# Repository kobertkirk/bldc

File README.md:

# 48 V / 35 A BLDC hub-motor controller

A KiCad hardware design plus STM32 firmware for a hall-sensored e-bike or scooter hub motor:

* **48 V nominal** (13S Li-ion, 54.6 V full). All power parts are rated 100 V and the TVS clamps at 60 V standoff.
* **35 A battery current limit** and 60 A phase current limit. Both are set in firmware and can be changed over UART.
* **Field-oriented control (FOC)** using the hall sensors, with angle interpolation, for quiet and smooth torque from standstill.
* **Throttle** input (standard 0.8–4.2 V hall throttle).
* **Momentary power button.** Press to switch on, hold for 2 s to switch off. Standby current is a few µA.
* **FWD/REV switch** input (switch to GND = reverse). There is also a **brake** input (switch to GND = cut power, optional regen).
* **UART telemetry and commands** (115200 8N1, 3.3 V). It streams every reading: voltage, currents, power, speed, temperatures, throttle, direction, faults, limits and energy used.
* **Auto-detect** measures motor R and L and learns the hall-sensor table, so any 120° hall hub motor works without setting angles by hand.

```
hardware/
  kicad/                 KiCad project (bldc48.kicad_pro): 4-sheet schematic + routed 4-layer PCB
  renders/               3D renders, routing/layer images, bldc48.glb 3D model
  bldc48-schematic.pdf   schematic as PDF
  bom.csv                bill of materials
  tools/                 circuit.py (the netlist source), generators, autorouting, connectivity checker,
                         render3d/ (VRML export + headless three.js renderer)
firmware/
  src/                   STM32G431 firmware (register-level, no HAL)
  sim/                   closed-loop PC simulation of the firmware against a hub-motor model
  cmsis/                 ST / ARM CMSIS headers (Apache-2.0)
```

> **Status — read this before building.** The schematic is complete and has been checked pin by pin (see
> [Verification](#verification)). The 90 × 95 mm (3.5 × 3.7 in) 4-layer, two-sided PCB (rev F) is **fully routed and passes KiCad
> DRC with 0 violations and 0 unconnected pads**. The power stage is placed by script around fixed columns; the signal
> routing was done by an autorouter (Freerouting), a small grid router for what it leaves open, and scripted copper
> pours, so have it reviewed before ordering. The firmware compiles and passes a detailed simulation, but it has
> **not been run on real hardware**. Bring the first board up with the current-limited procedure in
> [First power-up](#first-power-up).

---

## Block diagram

```
 BAT+ ──┬── TVS ── 3×1000µF + 6×2.2µF ──┬────────────────────────────────────┐
        │                                │  3 × half bridge (6 × IPT015N10N5) │
        │        ┌──────── DRV8353RS ────┴── GHx / GLx gate drive, SHx sense  ├── MOTOR A/B/C
        │        │  charge pump, 6-95 V buck → +5 V ── AP2112 → +3.3 V        │
        ├─Q1─────┤  3 × current-sense amp (G=20) ◄── 0.5 mΩ low-side Kelvin shunts
        │ latch  │  SPI config / fault readout, nFAULT
  PWR ──┘        └──► STM32G431CB ◄── ISENSE A/B/C, VBUS, throttle, NTCs
  button               │  ▲
              UART ◄───┘  └── halls, FWD/REV, brake, button
```

## Connectors

| Ref | Connector | Pin 1 | Pin 2 | Pin 3 | Pin 4 | Pin 5 | Pin 6 |
|---|---|---|---|---|---|---|---|
| J1 / J2 | 12 AWG solder pads (2.8 mm hole), right of the bridge | BAT+ / BAT− | | | | | |
| J3–J5 | 12 AWG solder pads, one per phase column | MOTOR A / B / C | | | | | |
| HALL | JST-GH 6 | +5 V | GND | Hall A | Hall B | Hall C | Motor NTC (optional) |
| THROTTLE | JST-GH 3 | +5 V | Signal | GND | | | |
| FWD/REV | JST-GH 2 | DIR (to GND = reverse) | GND | | | | |
| BRAKE | JST-GH 2 | BRAKE (to GND = braking) | GND | | | | |
| POWER_BTN | JST-GH 2 | PWR_SW (momentary to GND) | GND | | | | |
| UART | JST-GH 4 | +3.3 V out | TX (board → host) | RX (host → board) | GND | | |
| SWD | JST-GH 5 | +3.3 V | SWDIO | SWCLK | NRST | GND | |

All signal connectors are JST-GH (1.25 mm, latching) along the bottom edge. The power button and all signal wires
carry 3.3–5 V only, never battery voltage, so a cheap handlebar button is fine. Battery and phase wires are **12 AWG
silicone wire soldered straight into the plated pads** (strip 4 mm, push through, solder from the top; the pads are
via-stitched to the pours on all layers). Strain-relieve the wires to the case or heat plate with a cable tie so the
joints never carry the cable's weight. Put an **XT90-S anti-spark connector** and a **40 A fuse** in the battery
lead: the board has no reverse-polarity or inrush protection.

## First power-up

1. Flash the firmware over SWD (`cd firmware && make flash`).
2. Use a **bench supply at 48 V with a 2 A current limit**. Connect the UART (3.3 V USB-serial adapter at 115200 baud)
   and the halls, but leave the motor phases disconnected. Press the power button: the green LED blinks and telemetry
   lines (`$TLM,...`) appear. Type `status`. You should see vbus ≈ 48 V and `faults NOT_DETECTED`. Type `drv`:
   it should report `nFAULT=high` and zero status words (the DRV8353RS took its SPI settings).
3. Connect the motor phases (any order) and the hall connector. **Lift the wheel** so it spins freely.
4. Type `detect`. The wheel turns slowly forwards and then backwards (about 15 s total). Expected result:
   `detect OK: R = … mOhm, L = … uH, halls learned`. Type `save`.
   *(No UART cable? Hold the brake and full throttle for 3 s right after power-up, then release the throttle. Detect
   runs and saves automatically.)*
5. With the wheel still lifted, apply a little throttle. If the wheel turns the wrong way, `set dir_invert 1` then `save`.
6. Raise the supply limit (or switch to the battery) and set your limits, e.g. `set i_batt_max 35`, `set i_phase_max 60`,
   then `save`.

## UART interface

Lines end with CR or LF. Replies start with `>`. Telemetry lines start with `$TLM` (default every 100 ms;
change with `stream <ms>` or `stream off`).

```
$TLM,ms,state,faults,limits,vbus,ibus,power,ia,ib,ic,id,iq,iq_ref,erpm,rpm,mod,thr_v,thr_pct,dir,brake,hall,t_fet,t_mot,wh,ah,wh_regen
$TLM,105500,IDLE,0000,00,51.99,0.00,0.0,-0.01,0.01,-0.10,0.06,-0.00,0.00,2670,116.1,0.000,0.849,0.0,FWD,0,4,25.0,nan,10.912,0.2224,0.000
```
(Real line from the simulation: a coasting wheel at 116 rpm, 52 V, throttle at rest. `t_mot` is `nan` when no motor
NTC is enabled.)

| Command | What it does |
|---|---|
| `help` | List the commands |
| `status` | Human-readable state, faults, voltage, current, rpm, temperatures and control-loop CPU load |
| `tlm` / `hdr` | Print one telemetry line / print the column names |
| `stream <ms>` / `stream off` | Set the periodic telemetry rate, or turn it off |
| `get [name]` | Show one parameter, or all of them (including the learned hall angles) |
| `set <name> <value>` | Change a parameter in RAM |
| `save` / `defaults` | Write the config to flash / reload the defaults into RAM |
| `detect` / `detect r` / `detect l` / `detect hall` | Run auto-detect: everything, or only R, L or the hall table |
| `clear` | Clear latched faults |
| `drv` | DRV8353RS fault/status words, live and as captured at the last driver trip |
| `off` / `reboot` | Power the board off / restart the MCU |

Main parameters (`get` lists them all): `i_phase_max` 60 A, `i_batt_max` 35 A, `i_batt_regen` 5 A, `i_brake` 0 A (regen
on the brake input, off by default), `v_uv_start` 42 V / `v_uv_cut` 39 V (13S), `v_ov` 60 V, `t_fet_start` 80 °C /
`t_fet_max` 100 °C, `thr_min_v` 1.0 V / `thr_max_v` 4.0 V, `ramp_up` 100 A/s, `erpm_max` 0 (no speed limit),
`pole_pairs` 23 (only affects the rpm display), `mot_ntc_en` 0, `auto_off_min` 0.

| Fault bit (`faults` field, hex) | Meaning | Red LED blinks |
|---|---|---|
| 0x001 | overcurrent (80 A instantaneous phase-current trip) | 1 |
| 0x002 | overvoltage (> `v_ov`) | 2 |
| 0x004 | battery below `v_uv_cut` (no torque; information only) | short blink every 2 s |
| 0x008 | hall sensors invalid (000/111, e.g. unplugged) | 4 |
| 0x010 | throttle wire fault (< 0.4 V or > 4.7 V) | 5 |
| 0x020 | FET over-temperature or NTC broken | 6 |
| 0x040 | motor over-temperature (if `mot_ntc_en`) | 7 |
| 0x080 | halls not learned yet (run `detect`) | 8 |
| 0x100 | last detect failed | 9 |
| 0x200 | current-sensor offset out of range | 10 |
| 0x400 | throttle held at power-up | 11 |
| 0x800 | gate driver fault (DRV8353 nFAULT: VDS overcurrent, gate fault, UVLO, over-temperature); `drv` shows the fault words; the driver is re-initialised before it clears | 12 |

`limits` bits (why torque is reduced right now): 0x01 battery current, 0x02 phase current, 0x04 undervoltage
fold-back, 0x08 FET temperature, 0x10 motor temperature, 0x20 speed limit, 0x40 out of voltage (top speed),
0x80 stall protection.

Faults switch the gates off at once. They clear by themselves once the cause is gone and the throttle is back at
zero, so the motor can never restart while the throttle is held.

## How it works

**Power stage.** Six Infineon IPT015N10N5 (100 V, 1.5 mΩ, TOLL package) are driven directly by a TI DRV8353RS
smart gate driver (100 V, SPI). It sets the gate current itself (300 mA source / 600 mA sink, ≈100 ns edges on these
FETs), so there are no gate resistors; it adds 100 ns of its own dead time on top of the MCU's 400 ns and has a VDS
short-circuit trip (0.3 V, ≈110 A at 125 °C) behind the firmware's 80 A trip. Its SHx inputs sense each switch node
at the high-side source, right next to the gate pin. The MCU's TIM1 generates 20 kHz centre-aligned complementary
PWM (6-input mode). With the main output disabled, or with the driver asleep, all six gates are held low.

**Current sensing.** A 0.5 mΩ 4-terminal (Kelvin) shunt sits in each low-side source (Bourns CSS4J-4026R-L500F,
5 W). Its sense pads go to one of the DRV8353RS's three current-sense amplifiers (gain 20, biased to mid-rail), so full
scale is ±165 A per phase, comfortably above the 80 A hard trip (a compile-time check enforces this). The ADCs sample
while all three low-side FETs conduct, triggered by TIM1 channel 4 just before the counter peak. Above 90 % duty one
phase's low-side window is too short, so that phase's current is rebuilt from the other two (Ia + Ib + Ic = 0); the
duty is capped at 97 % so the bootstrap capacitors always recharge.

**Control.** The ADCs are triggered by the PWM timer once per period, and the injected-conversion interrupt runs the
FOC loop at 20 kHz:
- Clarke and Park transforms.
- PI current regulators on d and q, with BEMF/cross-coupling feed-forward and conditional-integration anti-windup.
- PWM delay compensation.
- Min/max SVPWM, capped at 97 % (low-side sensing needs a short low-side window; see above).

The rotor angle comes from the halls. Each hall edge gives the exact boundary angle, and between edges the angle is
extrapolated using a speed averaged over a full electrical revolution, which cancels sensor placement error. At
standstill the sector centre is used, which guarantees at least 86 % torque from the very first moment.

**Limits.**
- Throttle sets the torque (iq), with a ramp.
- Phase current limit.
- Battery current limit, from the power balance `I_bat = 1.5·vq·iq / Vbus`. In simulation it holds 34.8 A against a 35 A setting.
- Undervoltage, FET/motor temperature, speed and stall fold-backs.
- Instant 80 A hard trip and overvoltage trip.
- A direction change is only accepted once the wheel has stopped.

The motor flux linkage is learned while riding and used to re-engage smoothly at speed.

**Power latch.** When the button is pressed it pulls Q1's base (MMBTA92, 300 V PNP) low through 47 k and a diode.
Q1 enables the DRV8353RS's buck regulator. The MCU then sets PWR_HOLD, which turns on Q2 (MMBTA42) to keep Q1 on. A
BAT46W blocks the button-sense pull-up, so the latch cannot creep on through the unpowered 3.3 V rail. The buck's
enable divider also gives a ≈20 V UVLO. On shutdown the MCU first puts the gate driver to sleep, then releases the latch.

**Supplies.** The DRV8353RS's built-in 6–95 V buck (LM5008A core) makes +5 V for the halls, throttle and the
AP2112K-3.3 LDO; its 100 µH inductor is a 6 × 6 mm Bourns SRN6045TA. The gate drive comes from the DRV8353's own
charge pump (high side) and VGLS regulator (low side), so there is no 12 V rail and no separate gate-driver supply.
On power-up the firmware writes the driver's five configuration registers over SPI, reads them back and locks them;
a driver that does not answer stops the motor from starting (`drv` shows why).

## Verification

* `hardware/tools/check_netlist.py` exports KiCad's own netlist and checks that **every pin of all 133 parts** sits on
  the intended net, with no single-node nets. KiCad 7's CLI has no ERC, so this replaces it. A deliberately miswired
  pin is caught.
* KiCad DRC on the routed PCB: **0 violations, 0 unconnected pads, 0 footprint errors**, including the check that
  every footprint matches the stock KiCad library (report: `hardware/kicad/routing/drc.rpt`).
* `cd firmware && make sim` runs the **real** `motor.c`/`hall.c`/`cli.c` in closed loop against a model with:
  dead-time, PWM delay, ADC noise and offsets, 120° halls at an arbitrary offset, a 100 kg rider and a battery with
  internal resistance. It does this for two different motors. Results for motor 1:

  | Check | Result |
  |---|---|
  | Detect R / L / hall angles | 119.9 mΩ (120) / 259 µH (250) / 0.2° worst error |
  | Start from standstill, full throttle | torque ≥ 86 % of command from the first instant |
  | Peak phase current | 60.2 A (limit 60 A) |
  | Peak battery current (100 ms avg) | 34.3 A (limit 35 A) |
  | 120 A phase-short spike | hard trip, gates off within 200 µs |
  | Gate-driver fault (nFAULT) while riding | gates off within 2 PWM periods, driver re-initialised before restart |
  | High-duty current rebuild (low-side shunts) | exercised continuously at top speed, no faults |
  | Current-loop tracking | 0.47 A rms |
  | Top speed, 26″ wheel | ≈ 39 km/h (voltage limited) |
  | Coast, re-engage at speed, reverse, brake, throttle-wire break, hall unplug, low battery, overvoltage | all pass |

## Building the firmware

```
sudo apt install gcc-arm-none-eabi libnewlib-arm-none-eabi   # plus stlink-tools or openocd
cd firmware
make            # build/bldc48.elf/.bin/.hex  (~38 KB flash)
make flash      # st-flash, or: make flash-ocd
make sim        # closed-loop simulation on the PC
```

## Regenerating the hardware

The schematic, PCB and BOM are generated from `hardware/tools/circuit.py`, using symbols and footprints from the stock
KiCad libraries. After you edit the circuit, run `hardware/tools/regen.sh`. It needs KiCad ≥ 7; KiCad 8 and 9 open the
files directly.

`regen.sh` only places the parts. The board was then routed with
`hardware/tools/route_pcb.py --legacy --no-optimize --passes 30 --freerouting freerouting-1.9.0.jar`. This script:
- keeps tracks off the inner layers under the FETs, DC-link caps and shunts, and off the outer layers across the
  switch-node and low-side copper (rule areas)
- gives every GND pad outside the power stage its own via into the solid In1 plane, and puts a fixed "sense tap" via
  in each switch node next to the high-side gate pin for the DRV8353's SHx input
- routes the signals with Freerouting (headless, under `xvfb-run`)
- imports the result (KiCad 7 can only import a Specctra session from its GUI, so the script parses the file
  itself and restores any layer-change vias the router left out)
- `astar_route.py` is a small 4-layer grid router for connections Freerouting leaves open, keeping clear of the
  power copper
- adds the GND / +48V / +3V3 planes, the 35 A outer-layer pours and via arrays in the power pads, routes anything
  still cut off into its own pour, and stitches pour islands to the planes
- fills the zones and writes a DRC report

The routing session is saved in `hardware/kicad/routing/bldc48.ses` (with the DRC report next to it); `route_pcb.py
--ses ../kicad/routing/bldc48.ses` rebuilds a routed board from it, taking the part positions from the session. The
committed `bldc48.kicad_pcb` is the reference: a rebuild can differ in a few fan-out vias and then needs a DRC pass.

`hardware/tools/render3d/render.sh` exports the board to VRML with the KiCad 3D models (plus simple stand-ins for the
JST-GH connectors, the SRN6045 inductor and the DRV8353 QFN, whose models are not in the KiCad 7 library) and renders
the PNGs in `hardware/renders/` with three.js in headless Chromium; `layers.sh` makes the copper-layer images.

**Note:** regenerating overwrites placement and routing. For changes after this point, edit the board in KiCad and use
Tools → Update PCB from Schematic. The footprints are already linked to their schematic symbols for that.

### Board

| Overview | Power stage |
|---|---|
|  |  |
|  |  |

Routing (tracks only, pours hidden): 

Copper layers: [top](hardware/renders/bldc48-layer-top.png) · [inner 1, GND](hardware/renders/bldc48-layer-in1.png) ·
[inner 2, +48V/+3V3](hardware/renders/bldc48-layer-in2.png) · [bottom](hardware/renders/bldc48-layer-bottom.png)

Stackup as built: F.Cu power stage, gate drive and signals, with pours (switch nodes, low-side sources, +48V bus,
GND fill) · In1.Cu solid GND plane · In2.Cu +48V under the power stage and +3V3 fill elsewhere, plus signals ·
B.Cu the same high-current pours under the bridge, the MCU and I/O parts, and signals. The inner planes are unbroken
under the FETs, DC-link caps and shunts. 1666 track segments and 269 vias; each switch-node and low-side pour is one
unbroken piece on both outer layers (checked by script).

## Rev F: DRV8353RS, 90 × 95 mm

Rev E (180 × 69.5 mm) was still too big. Rev F redesigns the circuit around one TI DRV8353RS smart gate driver and
puts the parts on both sides of a **90 × 95 mm** board, **68 % of rev E's area** (3.5 × 3.7 in instead of
7.1 × 2.7 in).
- **One chip instead of eight.** The DRV8353RS replaces the three LM5109B gate drivers, the three INA240A1 current
  amplifiers and both LM5164 bucks: it has the gate drive (charge pump + low-side regulator, no 12 V rail), three
  current-sense amplifiers and a 6–95 V buck that makes the +5 V rail.
- **Low-side shunts.** The three 0.5 mΩ Kelvin shunts now sit in the low-side sources (the DRV8353's amplifiers are
  low-side). The firmware samples while all low-side FETs conduct and rebuilds the third current above 90 % duty.
- **Three 1000 µF / 100 V** cans (Aishi ERS1KM102M35OT, 18 × 35 mm) in a column next to the bridge, plus two 2.2 µF
  ceramics straight across each half bridge. 3000 µF is still 1.7 × rev B's 1760 µF. Cans can be bent over before
  soldering if the case is low.
- **12 AWG wires soldered straight into the board** instead of M5 bolt terminals: battery pads at the right of the
  bridge, one motor pad per phase column. JST-GH (1.25 mm, latching) for all signal connectors.
- **Two-sided assembly.** Power stage, gate driver, supply and connectors on top; MCU, its filters and the I/O
  conditioning on the bottom, outside the heat-plate area under the FETs.
- The phase columns run C-B-A from left to right, following the DRV8353's pin order, so no phase's gate drive crosses
  another's. The labels are only names: auto-detect learns the hall/phase order.
- Signal tracks 0.2 mm with 0.15 mm clearance (JLCPCB's 4-layer minimum is 0.09 mm). The +48 V and switch-node pours
  keep 0.5 mm.

Each phase is a column: high-side FET, low-side FET, shunt, two 2.2 µF ceramics and the motor wire pad on the switch
node beside the FETs. The heat plate goes under the bridge (bottom side, no parts there).

## Ordering from JLCPCB (rough cost)

These are estimates from JLCPCB's published pricing and LCSC part prices in October 2026. Upload the files to get a
real quote, because their prices change often.

| Item (order of 5 assembled boards) | Approx. |
|---|---|
| 4-layer PCB 90 × 95 mm, 1.6 mm, 2 oz outer copper, 5 pcs | $30–50 |
| PCBA setup + stencils, **two-sided** (standard PCBA: both sides placed) | ≈ $50 |
| "Extended" LCSC part loading fee, ≈ $3 per unique part type (~22 types) | ≈ $65 |
| SMT + through-hole joints (≈ 530 SMT + 6 THT per board) | ≈ $10 |
| Parts (≈ $30/board, all from LCSC; the DRV8353RS is ≈ $6, the six FETs ≈ $15) | ≈ $150 |
| Shipping (DHL / FedEx) | $20–35 |
| **Total for 5** | **≈ $325–360, about $65–72 per board** |

The five 12 AWG wire pads are left for you to solder (wires are not assembled). Choosing JLCPCB's "economic" PCBA
is not possible for a board with parts on both sides; if cost matters more than size, rev E (one-sided, 180 ×
69.5 mm) is in the git history.

Every part in the BOM has an LCSC part number or is a generic resistor/capacitor/diode/connector that LCSC stocks in
quantity, so JLCPCB can build the whole board.
- The bulk capacitors are Aishi ERS1KM102M35OT (C724666): 1000 µF/100 V, 18 × 35 mm, 7.5 mm pitch, 10 000 h at
  105 °C. Aishi's "1K" voltage code is 100 V in its own scheme ("1B" is 80 V), and LCSC lists the part as 100 V.
- Ripple: at 35 A battery current the DC link carries roughly 17 A rms, ≈ 5.7 A per can with three cans; the ceramics
  take the high-frequency part. Expect the cans to run warm in sustained hard use: watch their temperature, or lower
  `i_batt_max` / `i_phase_max`, or fit higher-ripple parts (Panasonic EEU-FC2A102, Nichicon UHE2A102).
- The shunts are Bourns CSS4J-4026R-L500F (LCSC/JLCPCB C2076423, 0.5 mΩ ±1 %, 5 W, 4-terminal). The footprint is
  KiCad's `R_Shunt_Isabellenhuette_BVR4026` (same 10.6 mm span and pad layout).
- The DRV8353RS is TI DRV8353RSRGZR (LCSC C506246), VQFN-48 7 × 7 mm with an exposed pad. Its exposed pad has a
  thermal-via array into the GND plane; ask for the vias to be tented or plugged.
- Check that every part you order has a 100 V rating where the BOM needs one: the TOLL FETs, DRV8353RS, the
  1000 µF/100 V caps, the 100 V ceramics and the SS110 diode. Do not let the assembly service substitute
  lower-voltage parts.
- Set the stackup to 2 oz outer copper. JLCPCB's cheap 4-layer offer is 1 oz.
- JLCPCB only assembles from 2 boards upward, and the setup and part-loading fees are charged once per order, so
  most of the cost of a small order is fees.
- Board size: 90 × 95 mm (3.5 × 3.7 in), 1.6 mm thick. The 1000 µF caps are the tallest parts, so the assembled
  board is about 37 mm tall (less if the caps are bent over). Four M3 holes: two in the battery strip, two in the
  bottom corners.

## Design review (rev B, kept for reference)

A full review of rev A found and fixed these problems:

| Problem in rev A | Fix in rev B |
|---|---|
| BAT+ / BAT− were 5×10 mm SMD solder pads 7.5 mm apart (≈2.5 mm copper gap), 6 mm in from the edge; SMD pads tear off under 12 AWG wire strain | M5 plated bolt terminals for ring lugs, via-stitched to the planes, on the left edge 36 mm apart, TVS between them, large BAT+/BAT− silkscreen |
| Motor pads sat 38 mm below their shunts | M5 bolt terminals on the bottom edge straight below each shunt, labelled MOTOR A/B/C |
| **Overcurrent trip could never fire**: INA240A2 (gain 50) saturated the ADC at ±66 A, below the 80 A trip | INA240A1 (gain 20, ±165 A full scale); a compile-time assert keeps the trip inside the measurable range; new simulation test trips on a 120 A spike within 200 µs |
| INA240 inputs tapped the switch-node/phase copper anywhere, so pour resistance corrupted the current reading | 4-terminal Kelvin shunt (Bourns CSS4J-4026R-L500F, 5 W) with dedicated sense pads to the amplifier |
| FET temperature sensor TH1 was in the board corner, far from the FETs | TH1 next to the middle low-side FET |
| DC-link ceramics ~32 mm from the low-side sources (large switching loop) | Ceramics directly under each low-side FET's source leads; both FETs drain-tab up so the switch node is a short gap between them |
| Low-side gate on the far side of the FET from its driver | Driver beside the FET pair, both gate pins facing it |
| Router ran signals on In2 straight under the FETs, slotting the +48V plane between the drains and the ceramics | Rule area keeps tracks off both inner layers under the FETs, ceramics and shunts |
| 10 Ω gate resistors: ≈170 ns edges, ≈2.9 W switching loss per high-side FET at 35 A | 4.7 Ω: ≈100 ns edges, ≈1.7 W |
| 6 × 220 µF carried ≈2.8 A rms ripple each | 8 × 220 µF, ≈2.1 A each |
| Pours sized from pad centres missed the TOLL drain tabs' real outline (vias in the tabs connected on one layer only) | Pours drawn from the measured pad outlines; inner planes solid-connected to the power terminals |

Checks run on rev B: every symbol pin matches its footprint pad (29 symbol/footprint pairs), every pin of all 174
parts is on its intended net, every footprint matches the stock KiCad library, KiCad DRC 0 violations, firmware
simulation passes on two motors including the new overcurrent test.

## PCB layout rules

* Use 4 layers with 2 oz outer copper. Run 35 A battery and phase paths as wide pours on two or more layers,
  stitched with many vias. Rule areas keep signal tracks off the switch-node and low-side copper on the top layer;
  do not route across them.
* Keep each half-bridge loop (high FET → low FET → 2.2 µF ceramics) as small as possible. The bulk caps sit right
  next to the bridge.
* Give the FET drain/source pads thermal-via arrays down to the bottom pours. Bolt the board to an aluminium plate or
  the case through a thermal pad under the bridge (no parts on the bottom there). At 35 A, expect roughly 6–10 W of
  losses at full load.
* Route each shunt's sense pads (pins 2/3 of the 4-terminal shunt) to the DRV8353's SPx/SNx as a pair, with the
  1 nF filter caps at the driver.
* Keep the gate-drive traces short and away from the switch nodes; the DRV8353's SHx pin senses each switch node at
  the high-side source, next to the gate pin. Use one solid ground plane, and keep the MCU and analog parts away from
  the switching nodes.
* Keep TH1 (the NTC) next to the low-side FETs, which run hottest.

## Things to double-check against datasheets before ordering

* The DRV8353RS buck (LM5008A core) component values (RT / shutdown divider, 100 µH inductor, 4.02 k / 4.02 k
  feedback divider, 8.2 k / 47 nF / 330 pF ripple injection) were chosen with the datasheet formulas but not run
  through TI WEBENCH.
* The DRV8353's gate-current setting (300 mA / 600 mA) and the gate-drive trace lengths: the longest gate trace is
  ≈ 60 mm (phase C high side). The driver's current-mode drive tolerates this, but look at the gate waveform on the
  first board and lower IDRIVE if it rings.
* The bulk capacitor ripple rating (≈ 5.7 A rms per can at 35 A battery current; see above).
* Choose `v_uv_*` for your pack. The defaults are for 13S.

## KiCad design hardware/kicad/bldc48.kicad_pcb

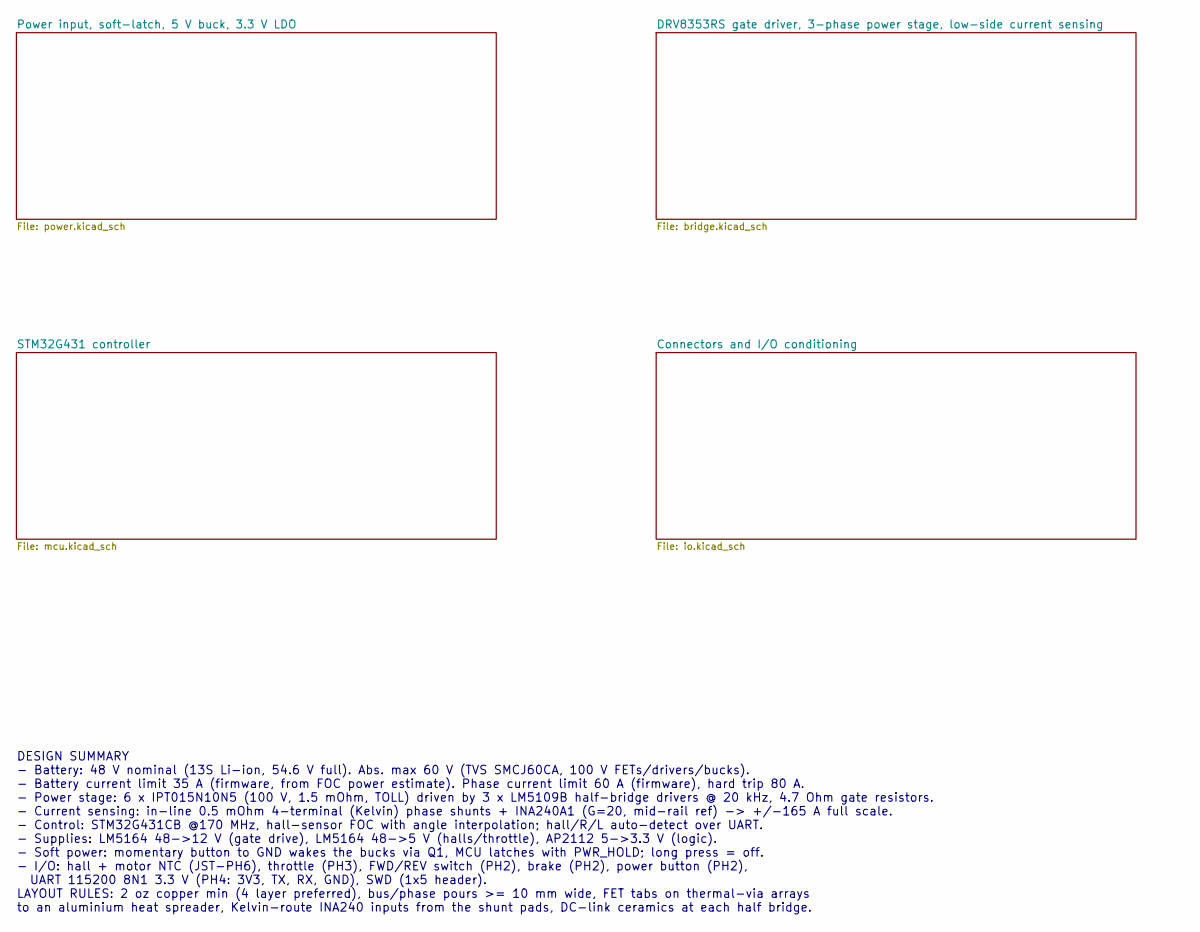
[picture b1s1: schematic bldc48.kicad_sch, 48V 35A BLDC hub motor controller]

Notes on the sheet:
DESIGN SUMMARY - Battery: 48 V nominal (13S Li-ion, 54.6 V full). Abs. max 60 V (TVS SMCJ60CA, 100 V FETs/drivers/bucks). - Battery current limit 35 A (firmware, from FOC power estimate). Phase current limit 60 A (firmware), hard trip 80 A. - Power stage: 6 x IPT015N10N5 (100 V, 1.5 mOhm, TOLL) dri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

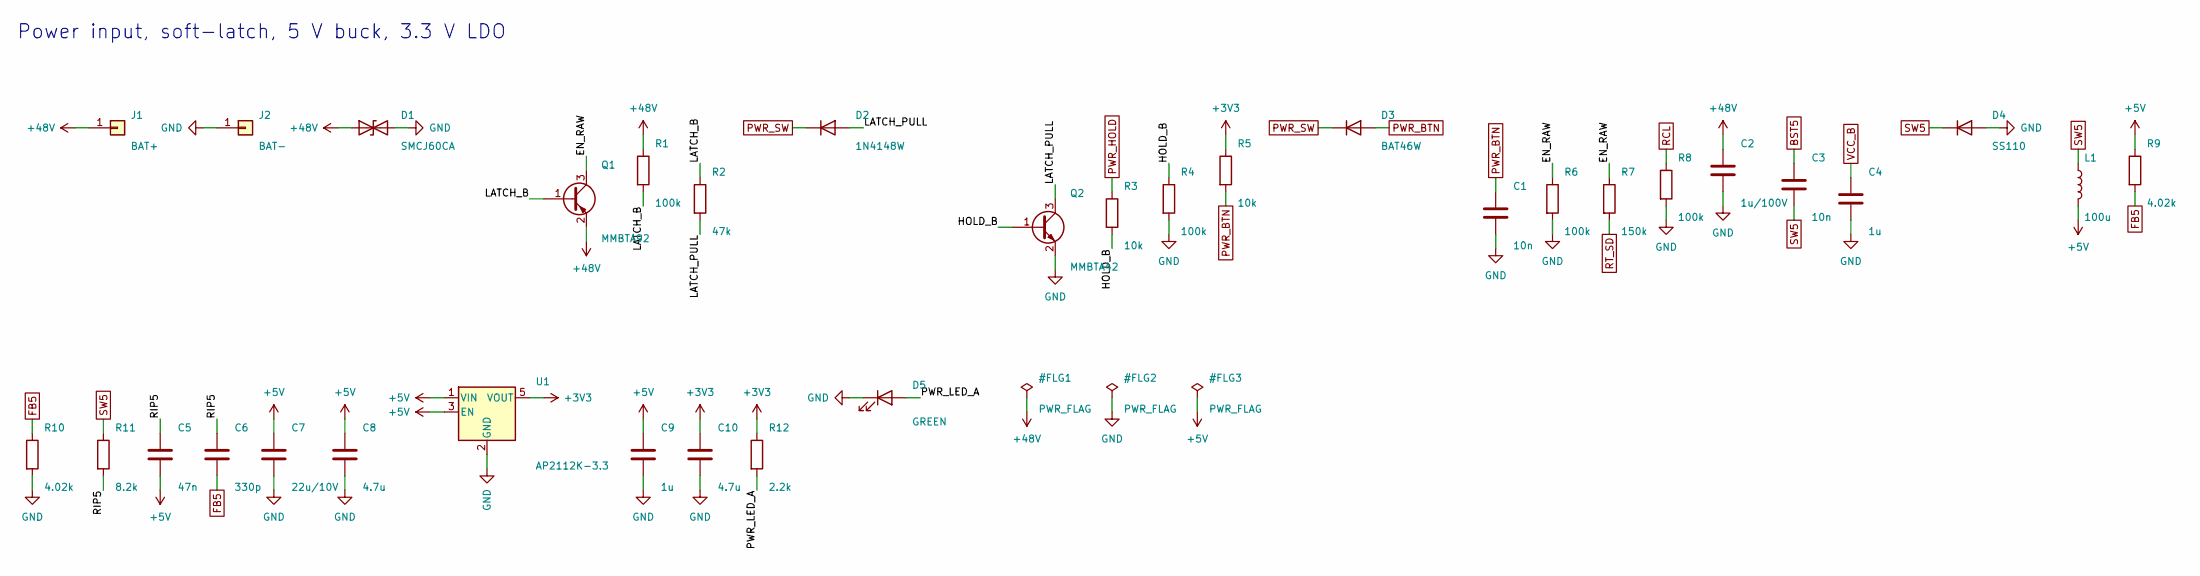
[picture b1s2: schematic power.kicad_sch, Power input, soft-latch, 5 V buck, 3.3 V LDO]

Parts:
C1, C3: 10n; C_0603_1608Metric
C2: 1u/100V; C_0805_2012Metric
C4, C9: 1u; C_0603_1608Metric
C5: 47n; C_0603_1608Metric
C6: 330p; C_0603_1608Metric
C7: 22u/10V; C_1210_3225Metric
C8, C10: 4.7u; C_0805_2012Metric
D1: SMCJ60CA; D_SMC
D2: 1N4148W; D_SOD-123
D3: BAT46W; D_SOD-123
D4: SS110; D_SMA; MPN 100 V 1 A Schottky, SMA (e.g. MDD SS110)
D5: GREEN; LED_0603_1608Metric
J1: BAT+; SolderWire_12AWG_D2.8mm_OD5.4mm; MPN 12 AWG wire, soldered
J2: BAT-; SolderWire_12AWG_D2.8mm_OD5.4mm; MPN 12 AWG wire, soldered
L1: 100u; L_Bourns_SRN6045TA; MPN Bourns SRN6045TA-101M or eq. (100 uH, I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
Q1: MMBTA92; SOT-23
Q2: MMBTA42; SOT-23
R1, R4, R6, R8: 100k; R_0603_1608Metric
R2: 47k; R_0603_1608Metric
R3, R5: 10k; R_0603_1608Metric
R7: 150k; R_0603_1608Metric
R9, R10: 4.02k; R_0603_1608Metric
R11: 8.2k; R_0603_1608Metric
R12: 2.2k; R_0603_1608Metric
U1: AP2112K-3.3; SOT-23-5

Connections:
+3V3: C10.1, R5.1, R12.1, U1.5 (VOUT); also elsewhere on the board
+5V: C5.2, C7.1, C8.1, C9.1, L1.2, R9.1, U1.1 (VIN), U1.3 (EN); also elsewhere on the board
+48V: C2.1, D1.1 (A1), J1.1, Q1.2 (E), R1.1; also elsewhere on the board
BST5: C3.1; also elsewhere on the board
EN_RAW: Q1.3 (C), R6.1, R7.1
FB5: C6.2, R9.2, R10.1; also elsewhere on the board
GND: C1.2, C2.2, C4.2, C7.2, C8.2, C9.2, C10.2, D1.2 (A2), D4.2 (A), D5.1 (K), J2.1, Q2.2 (E), R4.2, R6.2, R8.2, R10.2, U1.2 (GND); also elsewhere on the board
HOLD_B: Q2.1 (B), R3.2, R4.1
LATCH_B: Q1.1 (B), R1.2, R2.1
LATCH_PULL: D2.2 (A), Q2.3 (C), R2.2
PWR_BTN: C1.1, D3.2 (A), R5.2; also elsewhere on the board
PWR_HOLD: R3.1; also elsewhere on the board
PWR_LED_A: D5.2 (A), R12.2
PWR_SW: D2.1 (K), D3.1 (K); also elsewhere on the board
RCL: R8.1; also elsewhere on the board
RIP5: C5.1, C6.1, R11.2
RT_SD: R7.2; also elsewhere on the board
SW5: C3.2, D4.1 (K), L1.1, R11.1; also elsewhere on the board
VCC_B: C4.1; also elsewhere on the board

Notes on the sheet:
Power input, soft-latch, 5 V buck, 3.3 V LDO

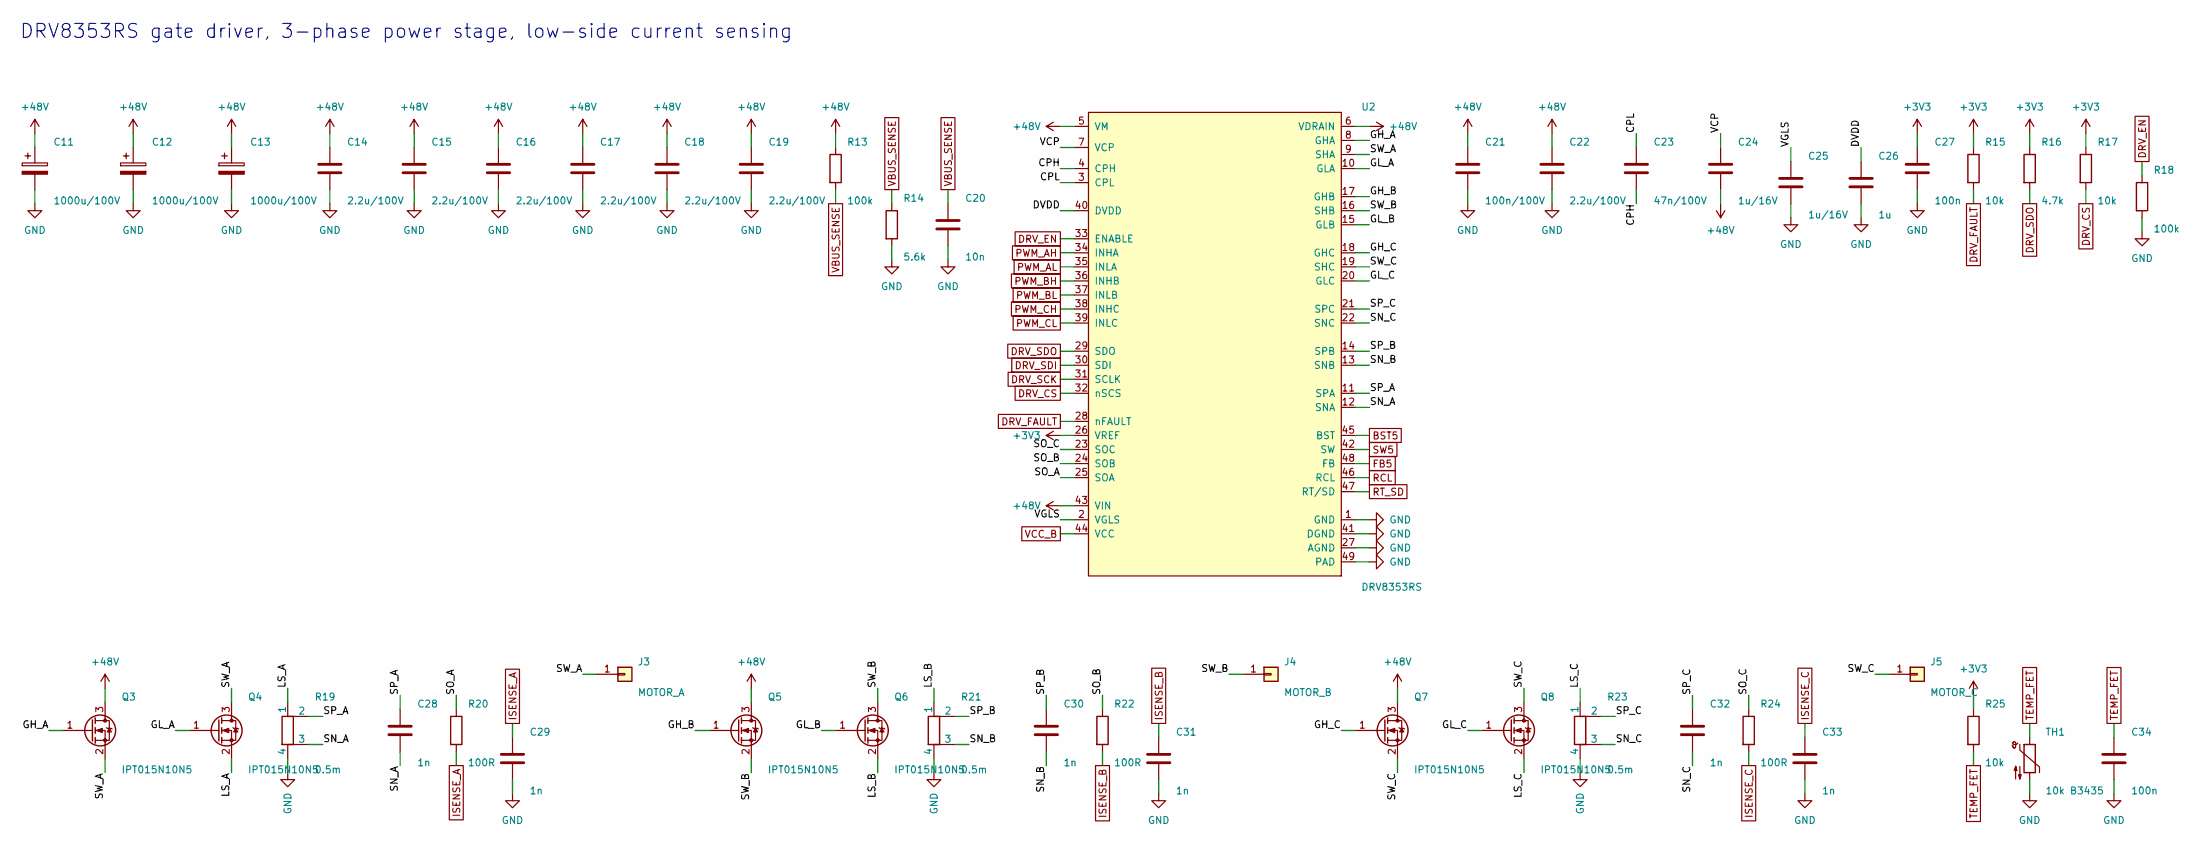
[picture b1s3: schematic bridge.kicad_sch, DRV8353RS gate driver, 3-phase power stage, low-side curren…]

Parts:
C11, C12, C13: 1000u/100V; CP_Radial_D18.0mm_P7.50mm; MPN Aishi ERS1KM102M35OT (LCSC C724666), 18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
C14, C15, C16, C17, C18, C19, C22: 2.2u/100V; C_1210_3225Metric
C20: 10n; C_0603_1608Metric
C21: 100n/100V; C_0805_2012Metric
C23: 47n/100V; C_0805_2012Metric
C24, C25: 1u/16V; C_0603_1608Metric
C26: 1u; C_0603_1608Metric
C27, C34: 100n; C_0603_1608Metric
C28, C29, C30, C31, C32, C33: 1n; C_0603_1608Metric
J3: MOTOR_A; SolderWire_12AWG_D2.8mm_OD5.4mm; MPN 12 AWG wire, soldered
J4: MOTOR_B; SolderWire_12AWG_D2.8mm_OD5.4mm; MPN 12 AWG wire, soldered
J5: MOTOR_C; SolderWire_12AWG_D2.8mm_OD5.4mm; MPN 12 AWG wire, soldered
Q3, Q4, Q5, Q6, Q7, Q8: IPT015N10N5; Infineon_PG-HSOF-8-1
R13, R18: 100k; R_0603_1608Metric
R14: 5.6k; R_0603_1608Metric
R15, R17, R25: 10k; R_0603_1608Metric
R16: 4.7k; R_0603_1608Metric
R19, R21, R23: 0.5m; R_Shunt_Isabellenhuette_BVR4026; MPN Bourns CSS4J-4026R-L500F (LCSC C2076423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
R20, R22, R24: 100R; R_0603_1608Metric
TH1: 10k B3435; R_0603_1608Metric; MPN Murata NCP18XH103F03RB (LCSC C13564)
U2: DRV8353RS; TI-RGZ-48-QFN; MPN TI DRV8353RSRGZR (LCSC C506246)

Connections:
+3V3: C27.1, R15.1, R16.1, R17.1, R25.1, U2.26 (VREF); also elsewhere on the board
+48V: C11.1, C12.1, C13.1, C14.1, C15.1, C16.1, C17.1, C18.1, C19.1, C21.1, C22.1, C24.2, Q3.3 (D), Q5.3 (D), Q7.3 (D), R13.1, U2.5 (VM), U2.6 (VDRAIN), U2.43 (VIN); also elsewhere on the board
BST5: U2.45 (BST); also elsewhere on the board
CPH: C23.2, U2.4 (CPH)
CPL: C23.1, U2.3 (CPL)
DRV_CS: R17.2, U2.32 (nSCS); also elsewhere on the board
DRV_EN: R18.1, U2.33 (ENABLE); also elsewhere on the board
DRV_FAULT: R15.2, U2.28 (nFAULT); also elsewhere on the board
DRV_SCK: U2.31 (SCLK); also elsewhere on the board
DRV_SDI: U2.30 (SDI); also elsewhere on the board
DRV_SDO: R16.2, U2.29 (SDO); also elsewhere on the board
DVDD: C26.1, U2.40 (DVDD)
FB5: U2.48 (FB); also elsewhere on the board
GH_A: Q3.1 (G), U2.8 (GHA)
GH_B: Q5.1 (G), U2.17 (GHB)
GH_C: Q7.1 (G), U2.18 (GHC)
GL_A: Q4.1 (G), U2.10 (GLA)
GL_B: Q6.1 (G), U2.15 (GLB)
GL_C: Q8.1 (G), U2.20 (GLC)
GND: C11.2, C12.2, C13.2, C14.2, C15.2, C16.2, C17.2, C18.2, C19.2, C20.2, C21.2, C22.2, C25.2, C26.2, C27.2, C29.2, C31.2, C33.2, C34.2, R14.2, R18.2, R19.4, R21.4, R23.4, TH1.2, U2.1 (GND), U2.27 (AGND), U2.41 (DGND), U2.49 (PAD); also elsewhere on the board
ISENSE_A: C29.1, R20.2; also elsewhere on the board
ISENSE_B: C31.1, R22.2; also elsewhere on the board
ISENSE_C: C33.1, R24.2; also elsewhere on the board
LS_A: Q4.2 (S), R19.1
LS_B: Q6.2 (S), R21.1
LS_C: Q8.2 (S), R23.1
PWM_AH: U2.34 (INHA); also elsewhere on the board
PWM_AL: U2.35 (INLA); also elsewhere on the board
PWM_BH: U2.36 (INHB); also elsewhere on the board
PWM_BL: U2.37 (INLB); also elsewhere on the board
PWM_CH: U2.38 (INHC); also elsewhere on the board
PWM_CL: U2.39 (INLC); also elsewhere on the board
RCL: U2.46 (RCL); also elsewhere on the board
RT_SD: U2.47 (RT/SD); also elsewhere on the board
SN_A: C28.2, R19.3, U2.12 (SNA)
SN_B: C30.2, R21.3, U2.13 (SNB)
SN_C: C32.2, R23.3, U2.22 (SNC)
SO_A: R20.1, U2.25 (SOA)
SO_B: R22.1, U2.24 (SOB)
SO_C: R24.1, U2.23 (SOC)
SP_A: C28.1, R19.2, U2.11 (SPA)
SP_B: C30.1, R21.2, U2.14 (SPB)
SP_C: C32.1, R23.2, U2.21 (SPC)
SW5: U2.42 (SW); also elsewhere on the board
SW_A: J3.1, Q3.2 (S), Q4.3 (D), U2.9 (SHA)
SW_B: J4.1, Q5.2 (S), Q6.3 (D), U2.16 (SHB)
SW_C: J5.1, Q7.2 (S), Q8.3 (D), U2.19 (SHC)
TEMP_FET: C34.1, R25.2, TH1.1; also elsewhere on the board
VBUS_SENSE: C20.1, R13.2, R14.1; also elsewhere on the board
VCC_B: U2.44 (VCC); also elsewhere on the board
VCP: C24.1, U2.7 (VCP)
VGLS: C25.1, U2.2 (VGLS)

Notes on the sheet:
DRV8353RS gate driver, 3-phase power stage, low-side current sensing

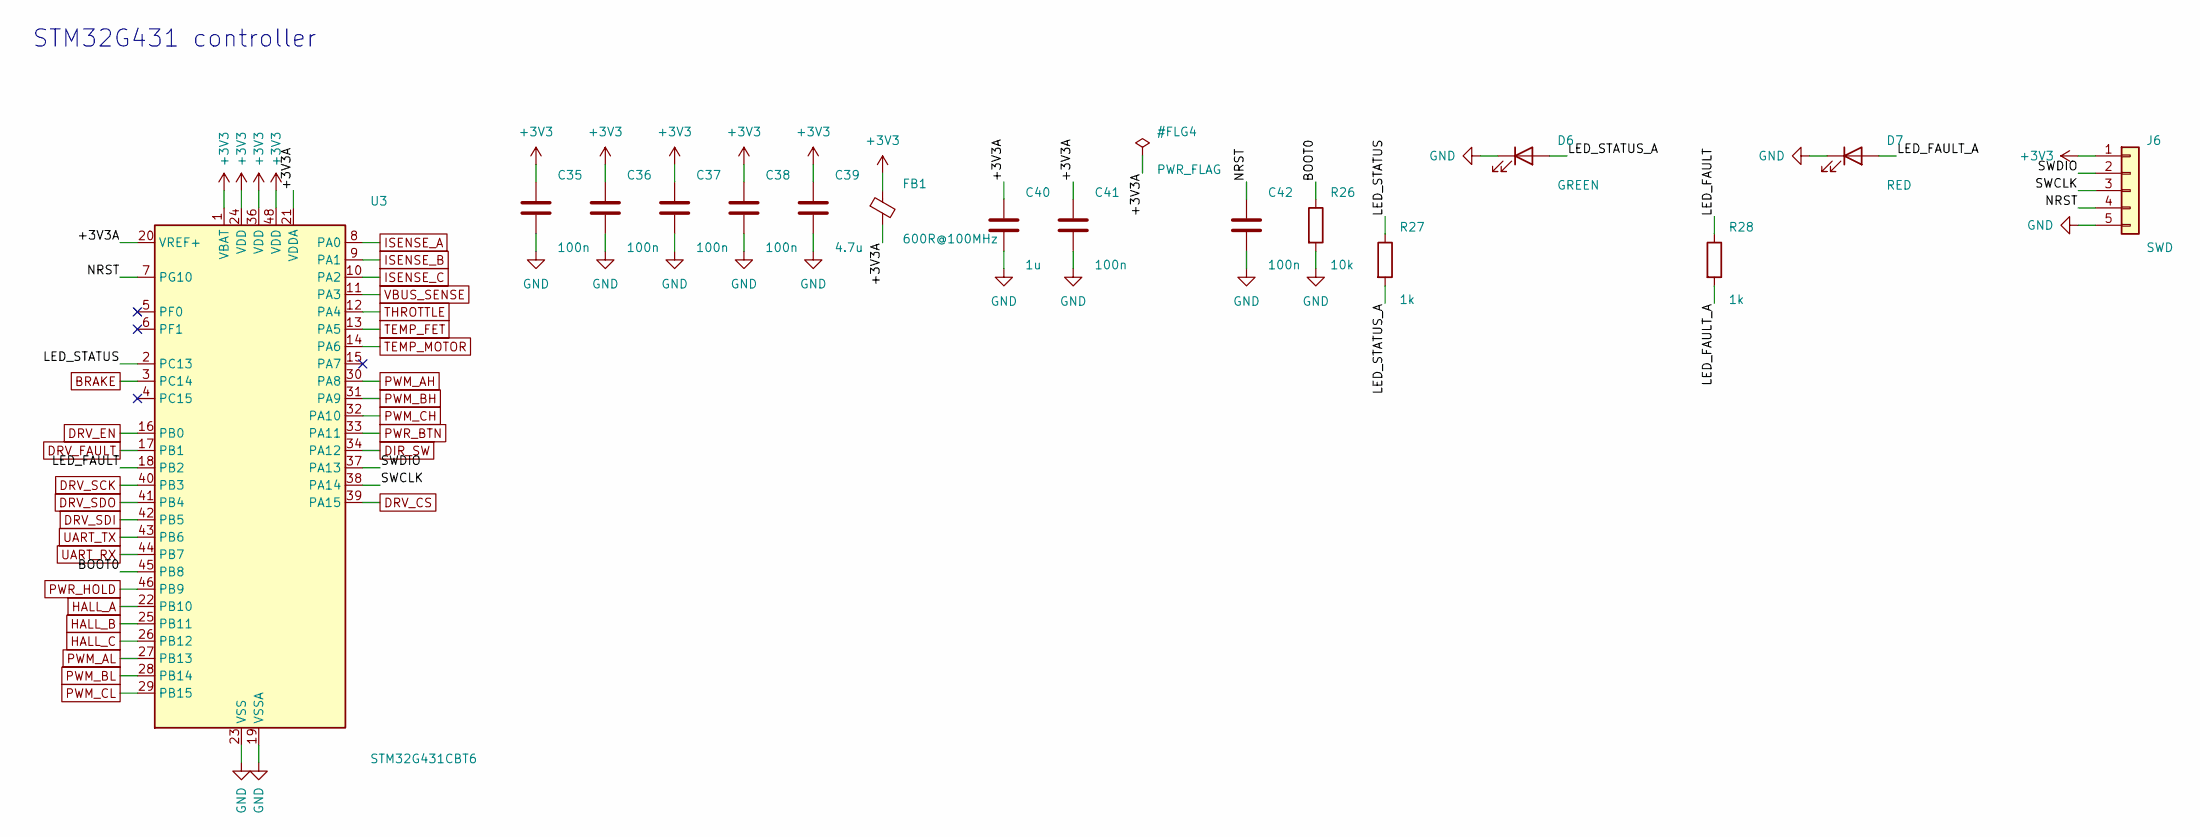
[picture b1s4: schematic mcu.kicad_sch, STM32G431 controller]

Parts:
C35, C36, C37, C38, C41, C42: 100n; C_0603_1608Metric
C39: 4.7u; C_0805_2012Metric
C40: 1u; C_0603_1608Metric
D6: GREEN; LED_0603_1608Metric
D7: RED; LED_0603_1608Metric
FB1: 600R@100MHz; L_0603_1608Metric
J6: SWD; JST_GH_BM05B-GHS-TBT_1x05-1MP_P1.25mm_Vertical; MPN JST BM05B-GHS-TBT (1.25 mm, latching)
R26: 10k; R_0603_1608Metric
R27, R28: 1k; R_0603_1608Metric
U3: STM32G431CBT6; LQFP-48_7x7mm_P0.5mm

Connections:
+3V3: C35.1, C36.1, C37.1, C38.1, C39.1, FB1.1, J6.1, U3.1 (VBAT), U3.24 (VDD), U3.36 (VDD), U3.48 (VDD); also elsewhere on the board
+3V3A: C40.1, C41.1, FB1.2, U3.20 (VREF+), U3.21 (VDDA)
BOOT0: R26.1, U3.45 (PB8)
BRAKE: U3.3 (PC14); also elsewhere on the board
DIR_SW: U3.34 (PA12); also elsewhere on the board
DRV_CS: U3.39 (PA15); also elsewhere on the board
DRV_EN: U3.16 (PB0); also elsewhere on the board
DRV_FAULT: U3.17 (PB1); also elsewhere on the board
DRV_SCK: U3.40 (PB3); also elsewhere on the board
DRV_SDI: U3.42 (PB5); also elsewhere on the board
DRV_SDO: U3.41 (PB4); also elsewhere on the board
GND: C35.2, C36.2, C37.2, C38.2, C39.2, C40.2, C41.2, C42.2, D6.1 (K), D7.1 (K), J6.5, R26.2, U3.19 (VSSA), U3.23 (VSS), U3.35 (VSS), U3.47 (VSS); also elsewhere on the board
HALL_A: U3.22 (PB10); also elsewhere on the board
HALL_B: U3.25 (PB11); also elsewhere on the board
HALL_C: U3.26 (PB12); also elsewhere on the board
ISENSE_A: U3.8 (PA0); also elsewhere on the board
ISENSE_B: U3.9 (PA1); also elsewhere on the board
ISENSE_C: U3.10 (PA2); also elsewhere on the board
LED_FAULT: R28.1, U3.18 (PB2)
LED_FAULT_A: D7.2 (A), R28.2
LED_STATUS: R27.1, U3.2 (PC13)
LED_STATUS_A: D6.2 (A), R27.2
NRST: C42.1, J6.4, U3.7 (PG10)
PWM_AH: U3.30 (PA8); also elsewhere on the board
PWM_AL: U3.27 (PB13); also elsewhere on the board
PWM_BH: U3.31 (PA9); also elsewhere on the board
PWM_BL: U3.28 (PB14); also elsewhere on the board
PWM_CH: U3.32 (PA10); also elsewhere on the board
PWM_CL: U3.29 (PB15); also elsewhere on the board
PWR_BTN: U3.33 (PA11); also elsewhere on the board
PWR_HOLD: U3.46 (PB9); also elsewhere on the board
SWCLK: J6.3, U3.38 (PA14)
SWDIO: J6.2, U3.37 (PA13)
TEMP_FET: U3.13 (PA5); also elsewhere on the board
TEMP_MOTOR: U3.14 (PA6); also elsewhere on the board
THROTTLE: U3.12 (PA4); also elsewhere on the board
UART_RX: U3.44 (PB7); also elsewhere on the board
UART_TX: U3.43 (PB6); also elsewhere on the board
VBUS_SENSE: U3.11 (PA3); also elsewhere on the board

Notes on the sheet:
STM32G431 controller

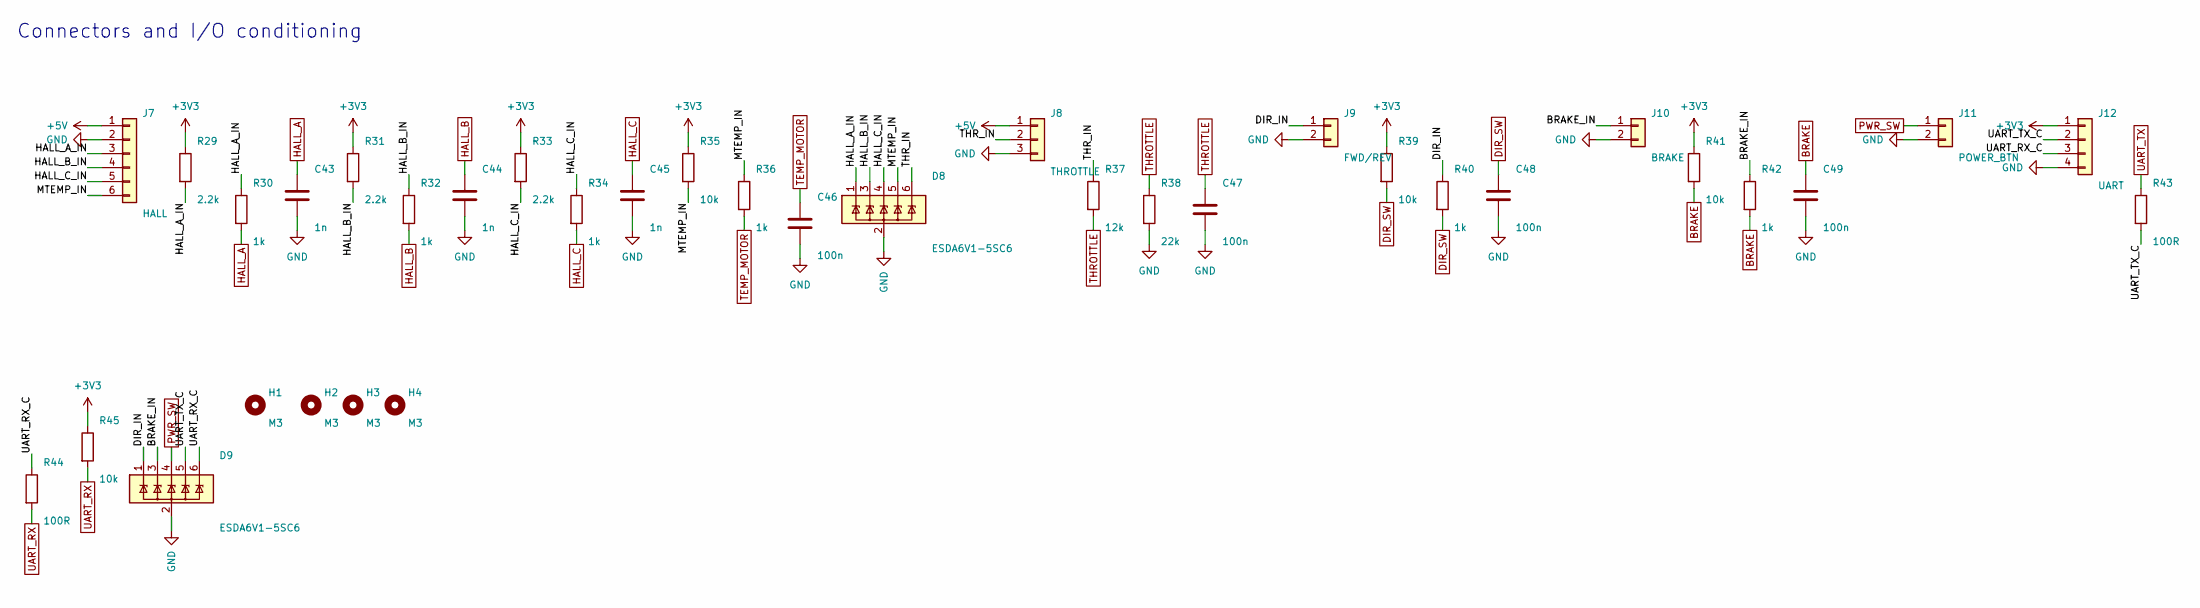
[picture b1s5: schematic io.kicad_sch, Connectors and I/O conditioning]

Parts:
C43, C44, C45: 1n; C_0603_1608Metric
C46, C47, C48, C49: 100n; C_0603_1608Metric
D8, D9: ESDA6V1-5SC6; SOT-23-6
H1, H2, H3, H4: M3; MountingHole_3.2mm_M3
J7: HALL; JST_GH_BM06B-GHS-TBT_1x06-1MP_P1.25mm_Vertical; MPN JST BM06B-GHS-TBT (1.25 mm, latching)
J8: THROTTLE; JST_GH_BM03B-GHS-TBT_1x03-1MP_P1.25mm_Vertical; MPN JST BM03B-GHS-TBT (1.25 mm, latching)
J9: FWD/REV; JST_GH_BM02B-GHS-TBT_1x02-1MP_P1.25mm_Vertical; MPN JST BM02B-GHS-TBT (1.25 mm, latching)
J10: BRAKE; JST_GH_BM02B-GHS-TBT_1x02-1MP_P1.25mm_Vertical; MPN JST BM02B-GHS-TBT (1.25 mm, latching)
J11: POWER_BTN; JST_GH_BM02B-GHS-TBT_1x02-1MP_P1.25mm_Vertical; MPN JST BM02B-GHS-TBT (1.25 mm, latching)
J12: UART; JST_GH_BM04B-GHS-TBT_1x04-1MP_P1.25mm_Vertical; MPN JST BM04B-GHS-TBT (1.25 mm, latching)
R29, R31, R33: 2.2k; R_0603_1608Metric
R30, R32, R34, R36, R40, R42: 1k; R_0603_1608Metric
R35, R39, R41, R45: 10k; R_0603_1608Metric
R37: 12k; R_0603_1608Metric
R38: 22k; R_0603_1608Metric
R43, R44: 100R; R_0603_1608Metric

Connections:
+3V3: J12.1, R29.1, R31.1, R33.1, R35.1, R39.1, R41.1, R45.1; also elsewhere on the board
+5V: J7.1, J8.1; also elsewhere on the board
BRAKE: C49.1, R41.2, R42.2; also elsewhere on the board
BRAKE_IN: D9.3 (IO2), J10.1, R42.1
DIR_IN: D9.1 (IO1), J9.1, R40.1
DIR_SW: C48.1, R39.2, R40.2; also elsewhere on the board
GND: C43.2, C44.2, C45.2, C46.2, C47.2, C48.2, C49.2, D8.2 (GND), D9.2 (GND), J7.2, J8.3, J9.2, J10.2, J11.2, J12.4, R38.2; also elsewhere on the board
HALL_A: C43.1, R30.2; also elsewhere on the board
HALL_A_IN: D8.1 (IO1), J7.3, R29.2, R30.1
HALL_B: C44.1, R32.2; also elsewhere on the board
HALL_B_IN: D8.3 (IO2), J7.4, R31.2, R32.1
HALL_C: C45.1, R34.2; also elsewhere on the board
HALL_C_IN: D8.4 (IO3), J7.5, R33.2, R34.1
MTEMP_IN: D8.5 (IO4), J7.6, R35.2, R36.1
PWR_SW: D9.4 (IO3), J11.1; also elsewhere on the board
TEMP_MOTOR: C46.1, R36.2; also elsewhere on the board
THROTTLE: C47.1, R37.2, R38.1; also elsewhere on the board
THR_IN: D8.6 (IO5), J8.2, R37.1
UART_RX: R44.2, R45.2; also elsewhere on the board
UART_RX_C: D9.6 (IO5), J12.3, R44.1
UART_TX: R43.1; also elsewhere on the board
UART_TX_C: D9.5 (IO4), J12.2, R43.2

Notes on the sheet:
Connectors and I/O conditioning

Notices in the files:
parts and their libraries:
TI RGZ0048A VQFN-48 7x7 mm (DRV8353RS). From the flatmcu project by GyrocopterLLC, MIT License, https://github.com/GyrocopterLLC/flatmcu
